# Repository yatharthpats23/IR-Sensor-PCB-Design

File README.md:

# IR Sensor PCB Design

## Overview
This project is an IR Sensor PCB designed using KiCad. The project includes schematic capture, PCB layout, and routing.

## Features
- IR transmitter and receiver interface
- Custom PCB layout
- Designed using KiCad
- Compact design

## Software Used
- KiCad

## Files Included
- IR SENSOR.kicad_sch (Schematic)
- IR SENSOR.kicad_pcb (PCB Layout)
- IR SENSOR.kicad_pro (Project File)

## Author
Yatharth Pathak

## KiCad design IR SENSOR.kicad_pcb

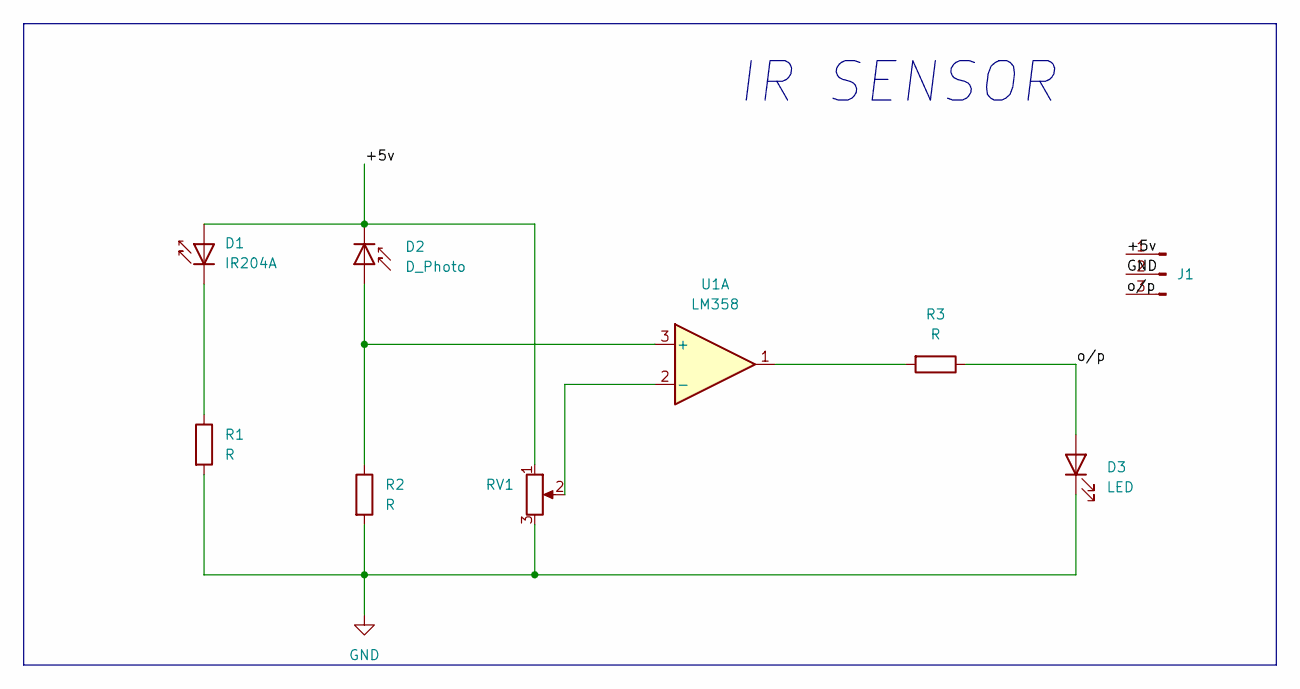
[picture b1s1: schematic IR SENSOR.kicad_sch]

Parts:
D1: IR204A; LED_1W_3W_R8
D2: D_Photo; LED_1W_3W_R8
D3: LED; LED_1W_3W_R8
J1: Conn_01x03_Pin; PinHeader_1x03_P2.54mm_Vertical
R1, R2, R3: R; R_0805_2012Metric
RV1: R_Potentiometer; Potentiometer_ACP_CA9-VSMD_Vertical
U1: LM358; SOIC-8-1EP_3.9x4.9mm_P1.27mm_EP2.514x3.2mm_ThermalVias

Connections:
/+5v: D1.2 (A), D2.1 (K), J1.1, RV1.1
/o/p: D3.2 (A), J1.3, R3.1
GND: D3.1 (K), J1.2, R1.2, R2.2, RV1.3
unnamed: D1.1 (K), R1.1
unnamed: D2.2 (A), R2.1, U1.3 (+)
unnamed: R3.2, U1.1
unnamed: RV1.2, U1.2 (-)

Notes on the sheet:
IR SENSOR

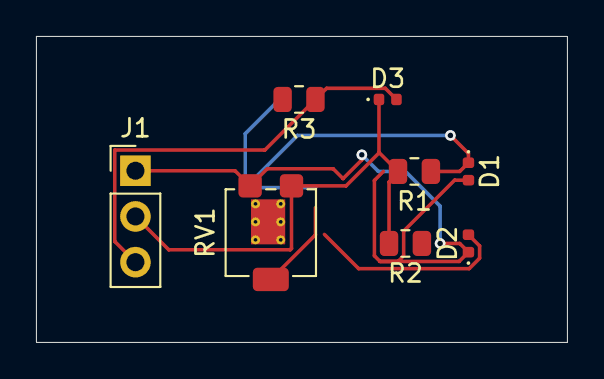
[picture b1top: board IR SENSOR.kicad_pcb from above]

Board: 2 copper layers, 29.5 x 17.0 mm, 9 parts (1 on the bottom side), 7 nets.

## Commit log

2026-06-09 Create README,md
